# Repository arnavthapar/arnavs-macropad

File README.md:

# Arnav's Macropad

Submission for Hackpad.
This is a simple macropad built of 5 switches, a rotary encoder, and 2 LEDs.
The switches are arranged in a row to allow quick and comfortable button presses.

The keys currently just type basic letters, as I made this to get experience with PCB and electronic design.
The PCB fits in the case below the top and will allow the buttons to be easily pressed. The rotary encoder also currently just types basic letters based on the angle.

Features:

- 5x Mechanical Switches
- 2x SK6812 Mini RGB LEDs
- Rotary Encoder

BOM:

- EC11 Rotary Encoder
- 5x Cherry MX Switches
- 5x Blank DSA Keycaps
- 2x SK6812 MINI LEDs
- XIAO RP2040
- 3d Printed Case (Top and Bottom)
- 4x Bolts

The schematic and PCB were made in KiCad, and the case was built in Fusion.

## Schematic

## PCB

The dimensions of the PCB are 99.25 mm by 44.25 mm.

## Case

The case has 5 cutouts for the keys and 2 smaller holes for the LED light to shine through. The large cutout on the bottom right is for the XIAO RP2040. It also has one cutout in the bottom left for the rotary encoder.

## Assembly

Assembling this is very easy.
Once the case is 3D printed, you can just slot in the PCB and bolt in the top; it should be instantly usable.

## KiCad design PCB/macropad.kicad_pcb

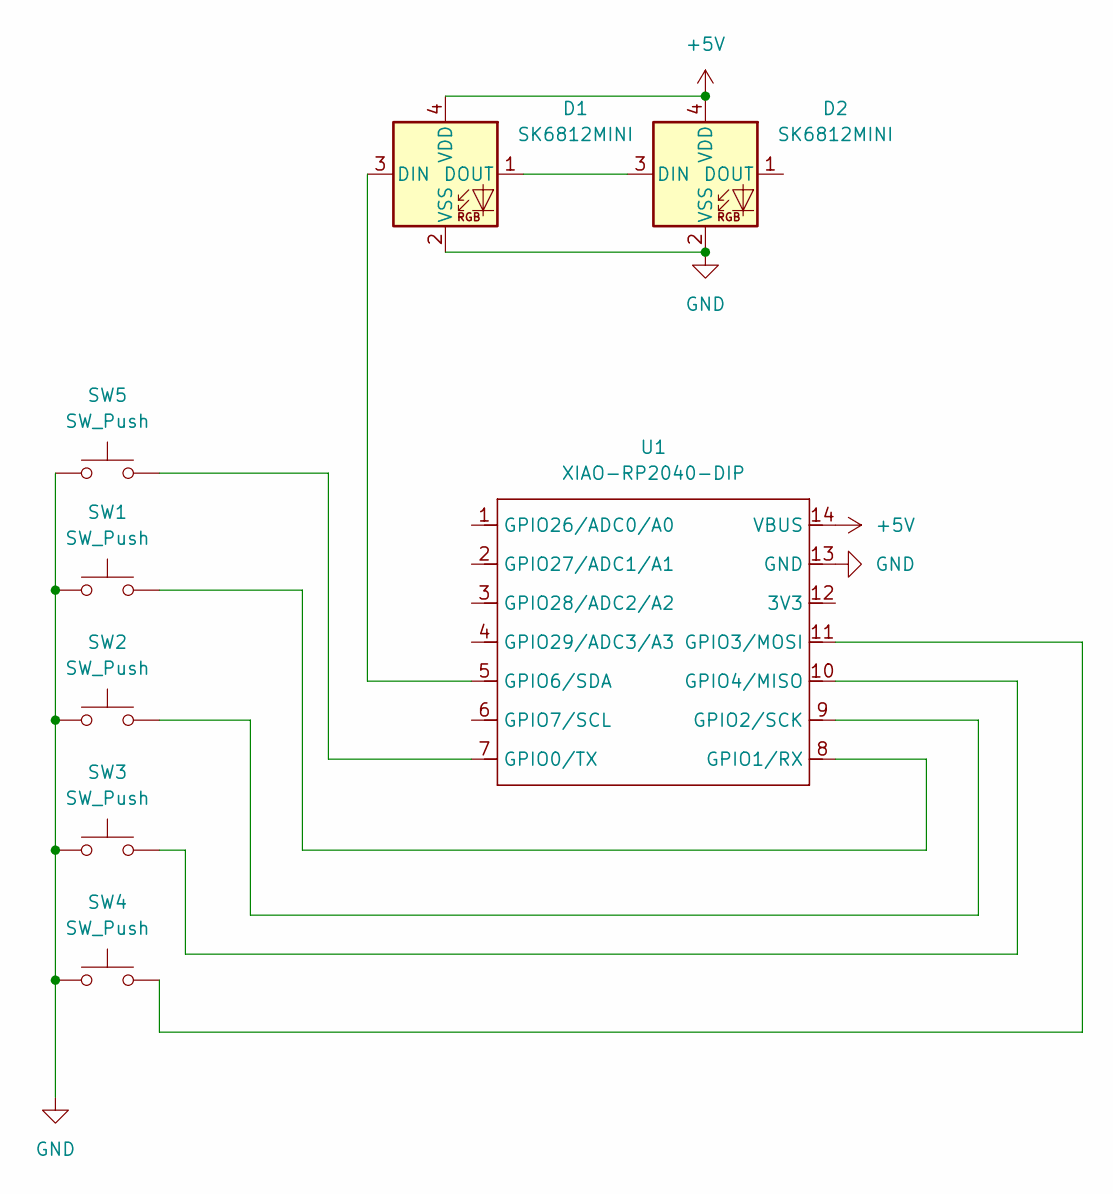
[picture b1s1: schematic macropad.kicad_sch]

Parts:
D1, D2: SK6812MINI; LED_SK6812MINI_PLCC4_3.5x3.5mm_P1.75mm
SW1, SW2, SW3, SW4, SW5: SW_Push; SW_Cherry_MX_1.00u_PCB
U1: XIAO-RP2040-DIP

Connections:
+5V: D1.4 (VDD), D2.4 (VDD), U1.14 (VBUS)
GND: D1.2 (VSS), D2.2 (VSS), SW1.1, SW2.1, SW3.1, SW4.1, SW5.1, U1.13 (GND); also elsewhere on the board
unnamed: D1.3 (DIN), U1.5 (GPIO6/SDA)
unnamed: D1.1 (DOUT), D2.3 (DIN)
unnamed: SW5.2, U1.7 (GPIO0/TX)
unnamed: SW1.2, U1.8 (GPIO1/RX)
unnamed: SW2.2, U1.9 (GPIO2/SCK)
unnamed: SW4.2, U1.11 (GPIO3/MOSI)
unnamed: SW3.2, U1.10 (GPIO4/MISO)
unnamed 9: U1.1 (GPIO26/ADC0/A0); also elsewhere on the board
unnamed 10: U1.2 (GPIO27/ADC1/A1); also elsewhere on the board
unnamed 11: U1.3 (GPIO28/ADC2/A2); also elsewhere on the board

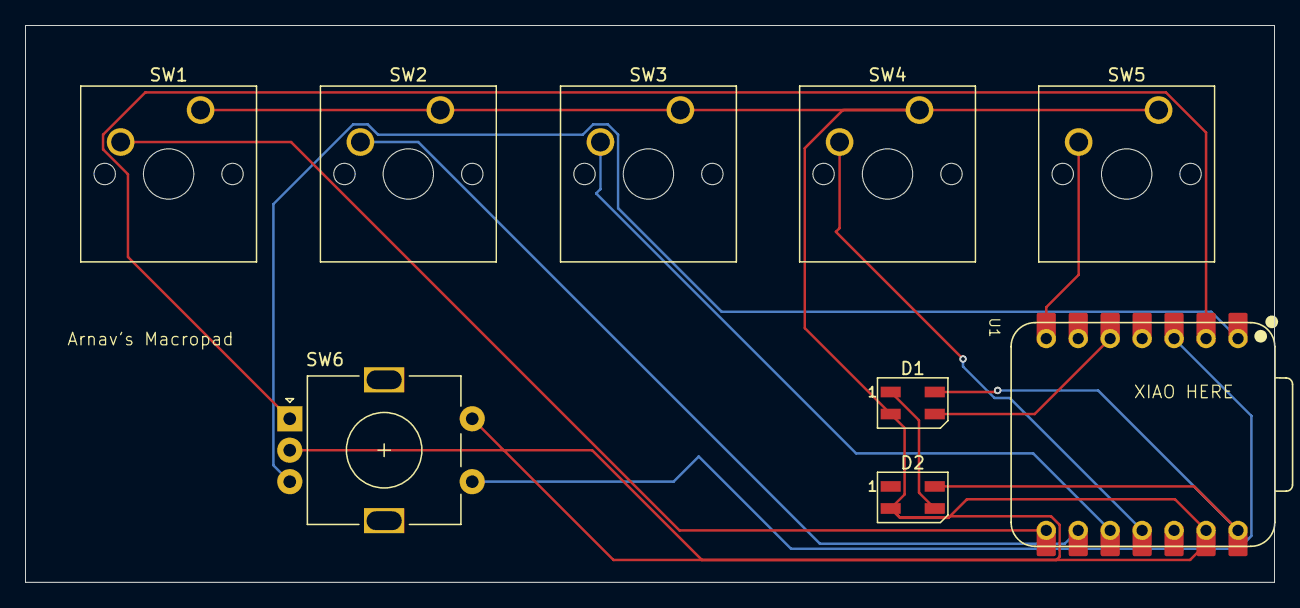
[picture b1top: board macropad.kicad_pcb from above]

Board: 2 copper layers, 99.2 x 44.2 mm, 9 parts (0 on the bottom side), 12 nets.

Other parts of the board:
SW6: RotaryEncoder_Switch; RotaryEncoder_Alps_EC11E-Switch_Vertical_H20mm

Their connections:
GND: SW6.C, SW6.S2; also elsewhere on the board
unnamed 9: SW6.B; also elsewhere on the board
unnamed 10: SW6.A; also elsewhere on the board
unnamed 11: SW6.S1; also elsewhere on the board

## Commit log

2025-11-29 base commit
2025-11-29 add images
2025-11-29 assets
2025-11-29 image fix
2025-11-29 md changes
2025-11-29 firmware
2025-11-29 led changes
2025-11-29 change case
2025-11-29 new image
2025-11-30 Create LICENSE
    Add MIT license.
2025-11-30 readme change
2025-12-01 add rotary encoder
2025-12-01 add kicad schematic file
2025-12-17 fix firmware

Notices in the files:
README.md:
License: MIT
